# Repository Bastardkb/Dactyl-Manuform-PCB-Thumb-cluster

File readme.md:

# Dactyl Manuform Mini PCB - thumbs

Flexible PCB made for the Dactyl Manuform Mini - with 5 thumb keys.

This repository contains all files necessary to order a PCB.

If you want to modify the design files, the Kicad sources are included (you will need a 5.99 nightly version).
If you just want to order the PCBs, check out the Release section which contain the gerber files.

## How to order

Order with a 0.6mm PCB thickness

## License

Licensed under CC BY-NC-SA 4.0

Copyright Quentin Lebastard 2021

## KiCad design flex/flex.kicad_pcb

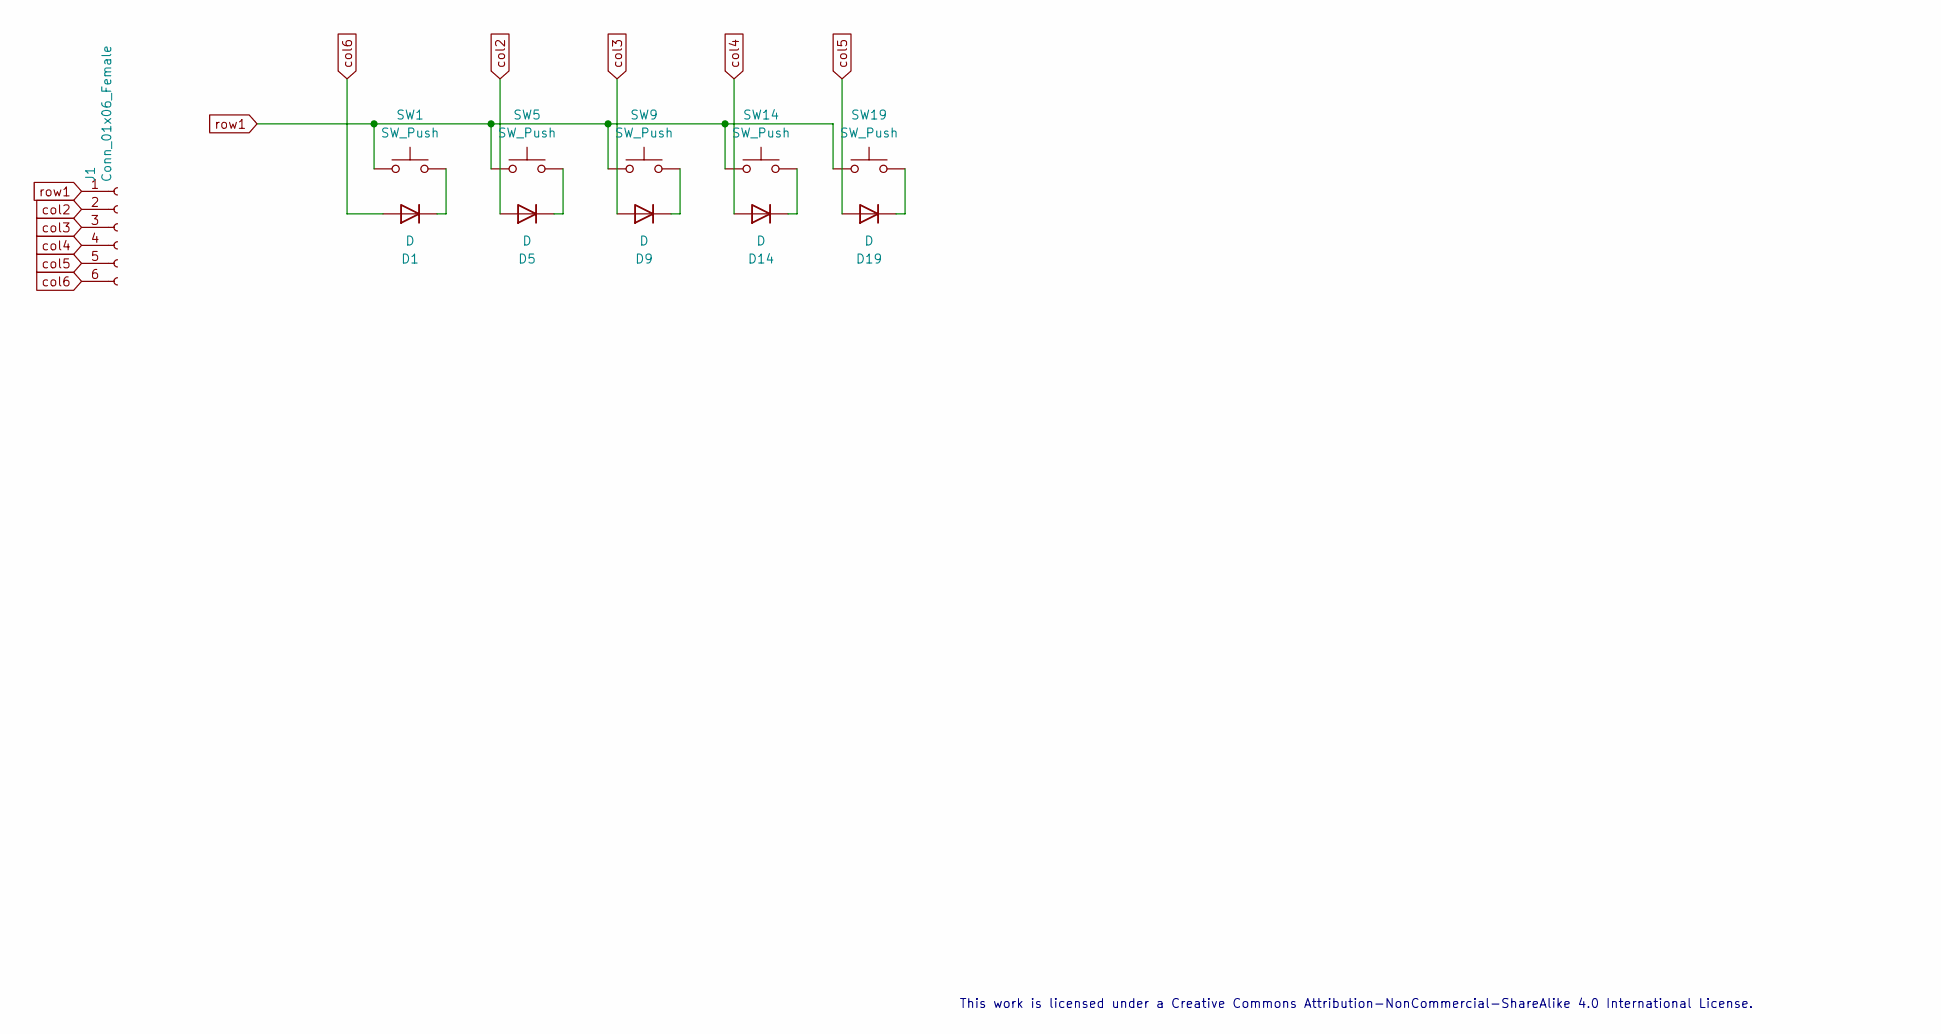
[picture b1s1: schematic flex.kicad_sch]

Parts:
D1, D5, D9, D14, D19: D; Diode_TH_SOD123
J1: Conn_01x06_Female; PinHeader_1x06_P2.54mm_Vertical
SW1, SW5, SW9, SW14, SW19: SW_Push; SW_MX_reversible

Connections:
unnamed: D1.1 (K), SW1.2
unnamed: D5.1 (K), SW5.2
unnamed: D9.1 (K), SW9.2
unnamed: D14.1 (K), SW14.2
unnamed: D19.1 (K), SW19.2
col2: D5.2 (A), J1.2
col3: D9.2 (A), J1.3
col4: D14.2 (A), J1.4
col5: D19.2 (A), J1.5
col6: D1.2 (A), J1.6
row1: J1.1, SW1.1, SW5.1, SW9.1, SW14.1, SW19.1

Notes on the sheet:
This work is licensed under a Creative Commons Attribution-NonCommercial-ShareAlike 4.0 International License.

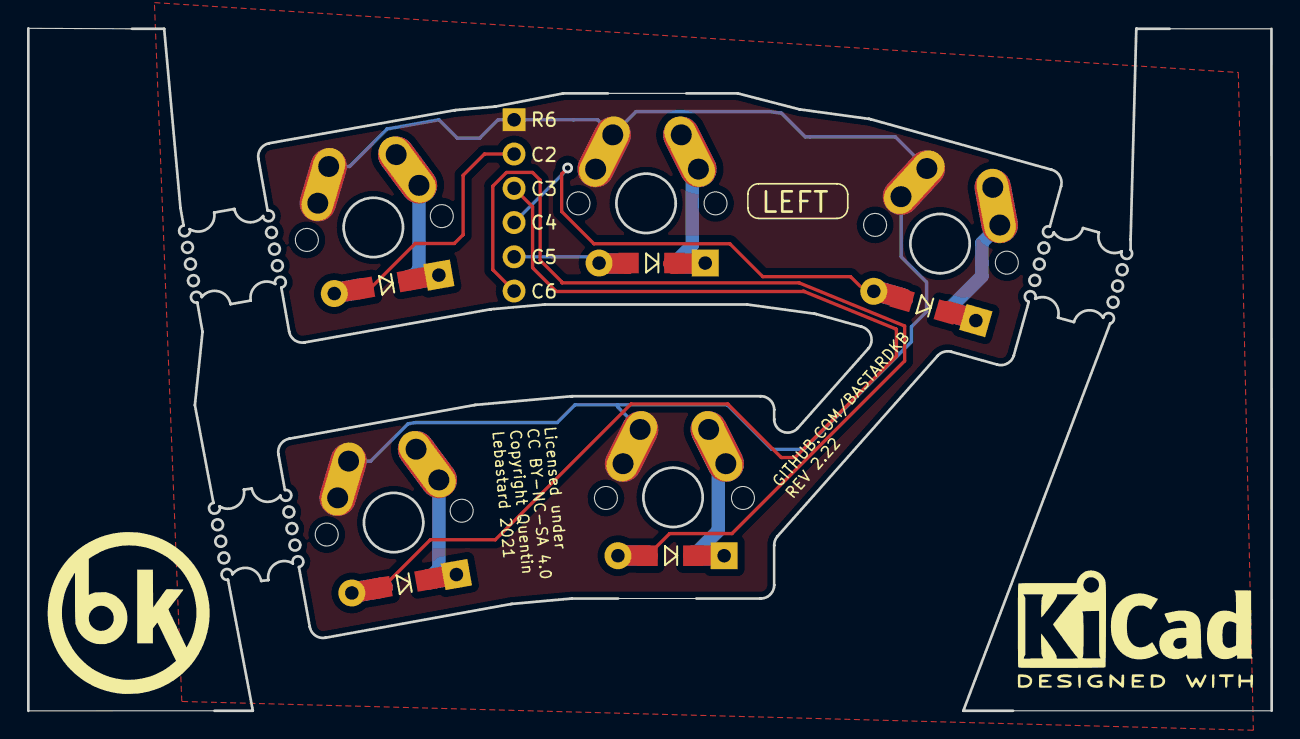
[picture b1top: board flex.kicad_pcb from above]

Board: 2 copper layers, 92.2 x 50.6 mm, 11 parts (0 on the bottom side), 11 nets.

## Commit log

2021-09-20 add files
